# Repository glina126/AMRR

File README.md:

# AMRR
AUTOMATA MODEL RAILROAD <br>
Have you ever dreamed of having your model railroad come to life all by itself? 
Have you ever wanted to have the trains be run by a computer while you are the head master who overlooks the situation? 
This project is exactly about that, automating your model railroad. AMRR - Automata Model Railroad.

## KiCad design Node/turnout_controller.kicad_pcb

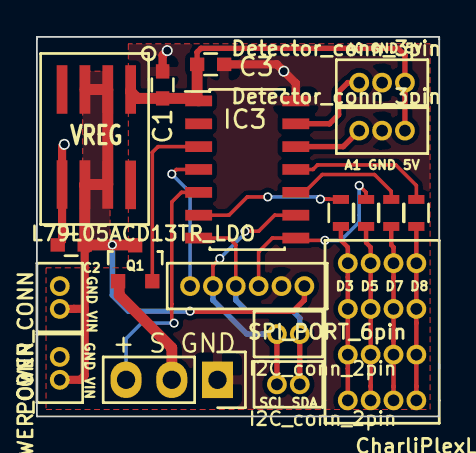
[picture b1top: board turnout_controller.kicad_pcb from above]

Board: 2 copper layers, 22.4 x 21.1 mm, 19 parts (0 on the bottom side), 19 nets.

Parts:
C1: 0.33uF; C_0603
C2: 0.1uF; C_0603
C3: C; C_0603
IC1: L79L05ACD13TR_LDO; SO8-L79L
IC2: CharliPlexLED-4pin; Charliplex_LED_4x4pin
IC3: ATTINY841-SSU; SOIC-14_3.9x8.7mm_Pitch1.27mm
Q1: NPN; SOT-23
R1, R2, R3, R4: R; R_0603
U1: SERVO_CONN_3pin; servo_conn_1x03
U2: SPI_PORT_6pin
U3, U4: Detector_conn_3pin; block_3pin_corrected
conn1, conn3: I2C_conn_2pin
conn2, conn4: POWER_CONN; PWR_CONN_1.27mm

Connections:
+5V: C1.1, C3.1, IC1.3, IC3.1, U3.3, U4.3
A0: IC3.13, U4.1
A1: IC3.12, U3.1
CP1: IC3.11, R4.2
CP2: IC3.10, R3.2
CP3: IC3.8, R2.2, U2.3
CP4: IC3.6, R1.2
GND: C1.2, C2.2, C3.2, IC1.2, IC3.14, U1.3, U2.2, U3.2, U4.2, conn2.2, conn4.2
unnamed: IC2.1, R4.1
unnamed: IC2.2, R3.1
unnamed: IC2.3, R2.1
unnamed: IC2.4, R1.1
RESET: IC3.4, U2.6
SCL: IC3.9, U2.5, conn1.2, conn3.2
SDA: IC3.7, U2.4, conn1.1, conn3.1
SERVO_POSITIVE: Q1.1, U1.2
SERVO_POWER: IC3.3, Q1.2
SERVO_SIGNAL: IC3.5, U1.1
VIN: C2.1, IC1.1, Q1.3, U2.1, conn2.1, conn4.1

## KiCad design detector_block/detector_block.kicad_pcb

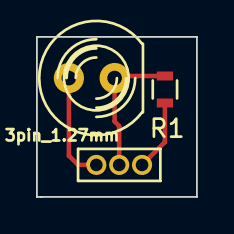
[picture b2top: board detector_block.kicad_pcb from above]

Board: 2 copper layers, 8.9 x 8.9 mm, 3 parts (0 on the bottom side), 3 nets.

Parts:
Ph1: Photoresistor; LED-5MM
R1: R; R_0603
conn1: 3pin_1.27mm; 1.27mm_1x3_detector

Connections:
unnamed: Ph1.1, conn1.1
unnamed: Ph1.2, R1.2, conn1.2
unnamed: R1.1, conn1.3

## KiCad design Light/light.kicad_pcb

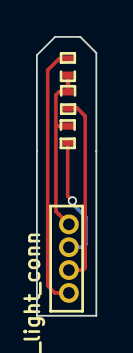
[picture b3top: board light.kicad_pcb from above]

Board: 2 copper layers, 3.3 x 15.5 mm, 4 parts (0 on the bottom side), 4 nets.

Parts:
D1, D2, D3: LED; SMD-0402_LED
U1: 4pin_light_conn; 4_pin_light_conn

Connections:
PIN1: D1.2, U1.1
PIN2: D2.2, U1.2
PIN3: D3.2, U1.3
VIN: D1.1, D2.1, D3.1, U1.4

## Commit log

2015-03-27 Finished Node, will go into master once back from fab and tested
2015-03-27 Create README.md
    created a readme
2015-03-27 Update README.md
    added <br>
2015-03-27 initial light design
2015-04-07 added necessary resistors for the charliplexed leds and flipped servo pins to match the servo female header
2015-04-07 changed links
2015-04-07 added gerber files
2015-04-07 changed light design
2015-04-07 removed an unnecessary resistor and redid the layout
2015-04-07 gerber files
2015-04-08 detector block
2015-04-08 added a panel version of the semaphore light
2015-04-08 final touches and gerber files
2015-04-25 version 0.2 - added extra footprint so that the node can serve as a relay. fixed the servo footprint.
